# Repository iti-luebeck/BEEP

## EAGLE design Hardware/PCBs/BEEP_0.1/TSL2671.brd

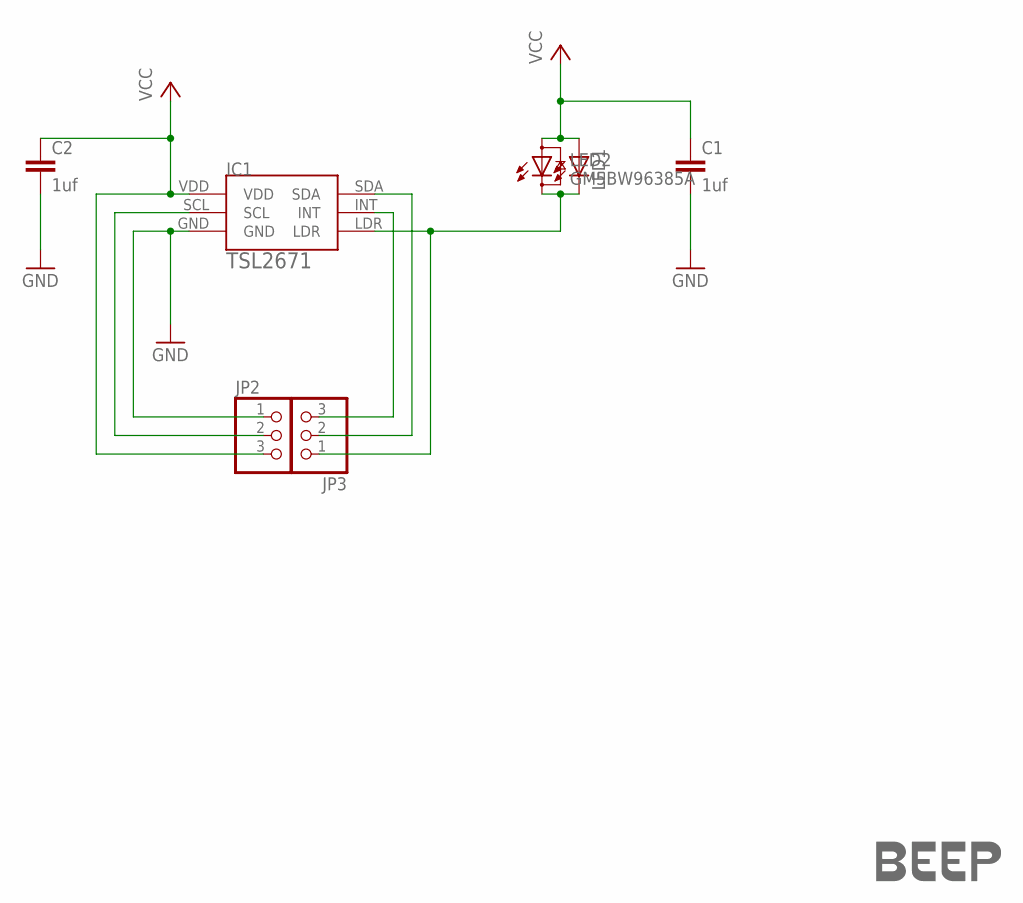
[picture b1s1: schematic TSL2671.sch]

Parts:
C1: 1uf; C025-025X050
C2: 1uf; C1206K
IC1: TSL2671
JP2, JP3: PINHD-1X3; 1X03
LED1: LED5MM
LED2: GM5BW96385A
U$1: LOGO-COPPER4; COPPER4

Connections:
GND: C1.2, C2.2, IC1.GND, JP2.1
unnamed: IC1.LDR, JP3.1, LED1.K (C), LED2.C
unnamed: IC1.SCL, JP2.2
unnamed: IC1.SDA, JP3.2
unnamed: IC1.INT, JP3.3
VCC: C1.1, C2.1, IC1.VDD, JP2.3, LED1.A, LED2.A

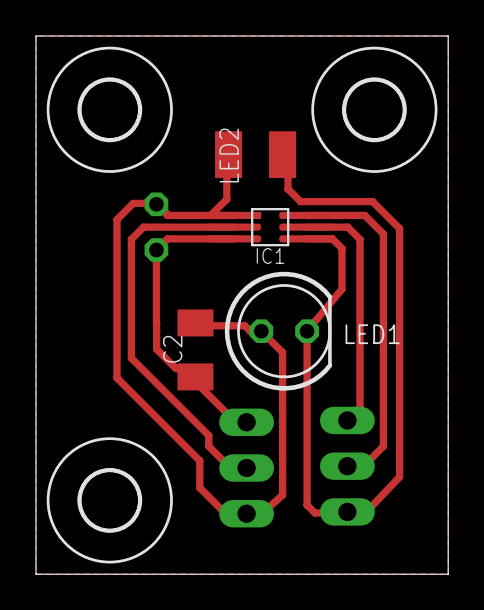
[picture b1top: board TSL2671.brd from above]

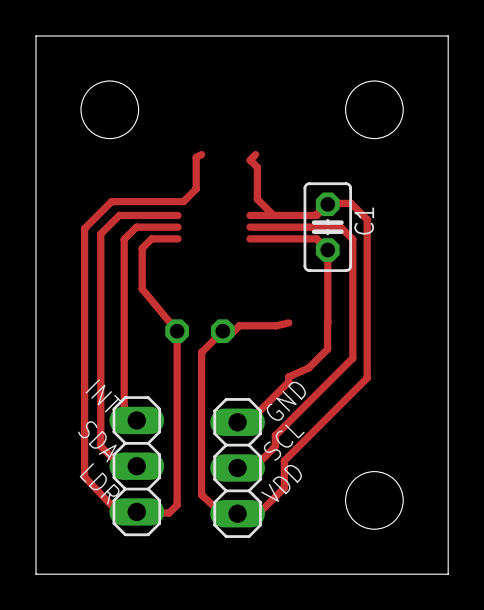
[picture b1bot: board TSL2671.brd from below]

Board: 2 copper layers, 22.9 x 29.9 mm, 11 parts (3 on the bottom side), 6 nets.

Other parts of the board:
U$2, U$3, U$4: 3,2

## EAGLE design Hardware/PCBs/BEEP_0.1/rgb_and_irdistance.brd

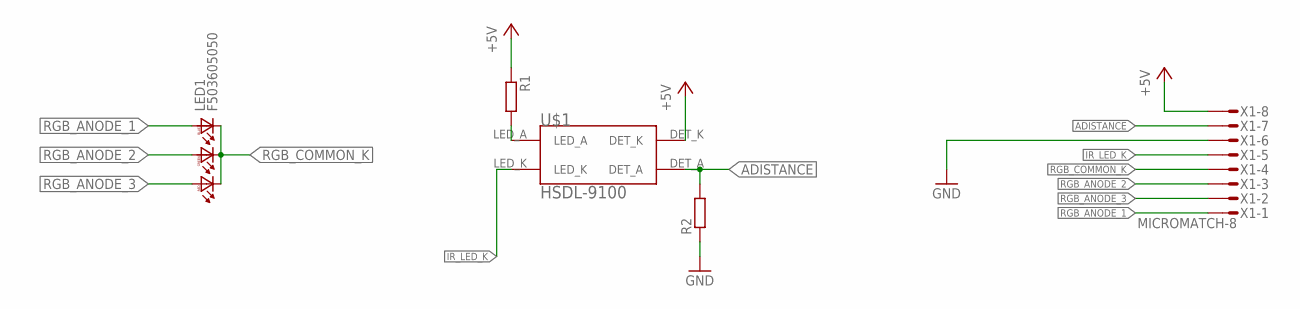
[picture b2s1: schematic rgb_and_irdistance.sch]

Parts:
LED1: F503605050; 5050LED
R1, R2: R-EU_R0603; R0603
U$1: HSDL-9100
X1: MICROMATCH-8

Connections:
+5V: R1.1, U$1.DET_K, X1.8
ADISTANCE: R2.2, U$1.DET_A, X1.7
GND: R2.1, X1.6
IR_LED_K: U$1.LED_K, X1.5
unnamed: R1.2, U$1.LED_A
RGB_ANODE_1: LED1.B1 (BA), X1.1
RGB_ANODE_2: LED1.G1 (GA), X1.3
RGB_ANODE_3: LED1.R1 (RA), X1.2
RGB_COMMON_K: LED1.B2 (BC), LED1.G2 (GC), LED1.R2 (RC), X1.4

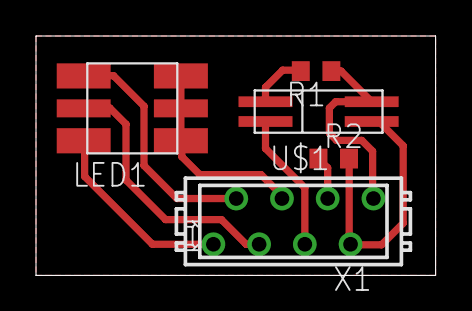
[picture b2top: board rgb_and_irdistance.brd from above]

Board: 2 copper layers, 22.2 x 13.3 mm, 5 parts (0 on the bottom side), 9 nets.

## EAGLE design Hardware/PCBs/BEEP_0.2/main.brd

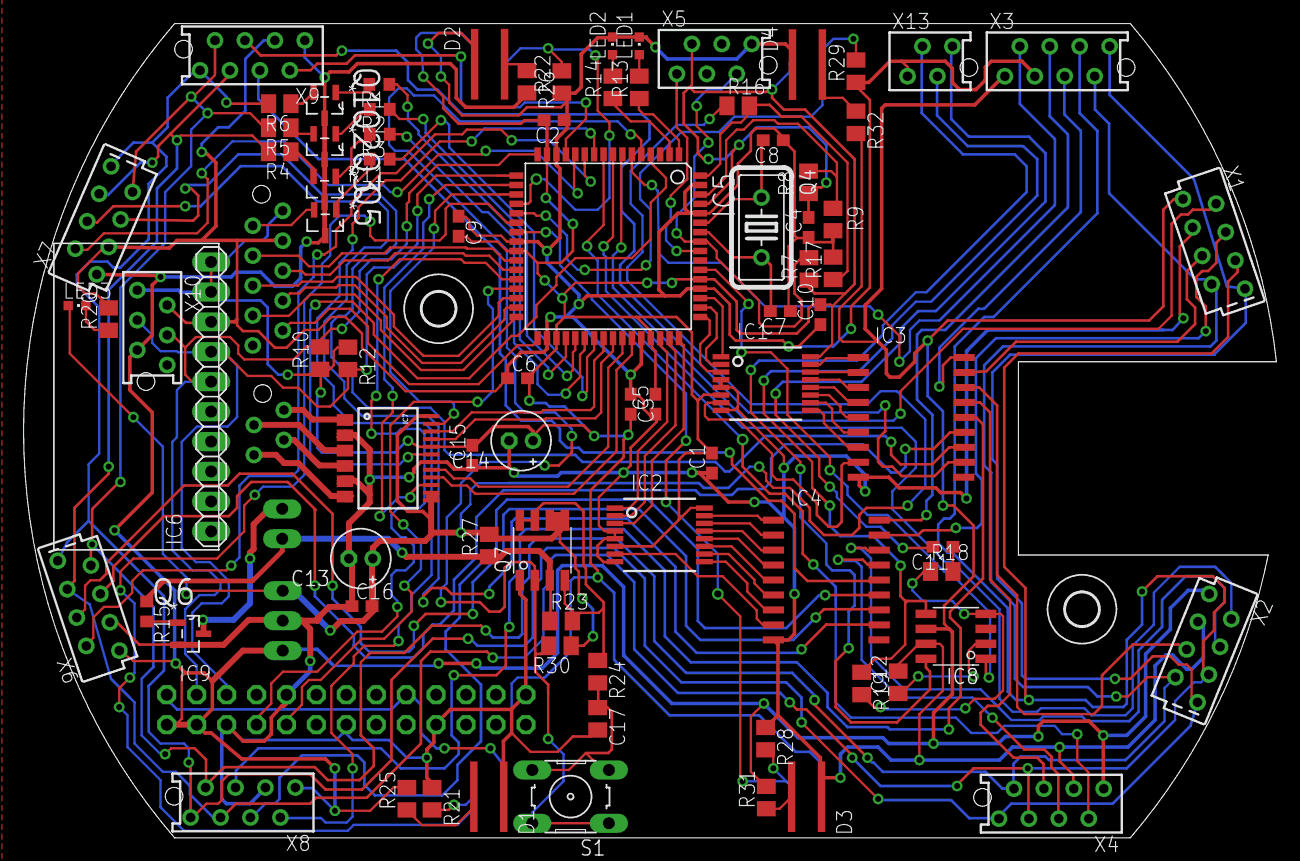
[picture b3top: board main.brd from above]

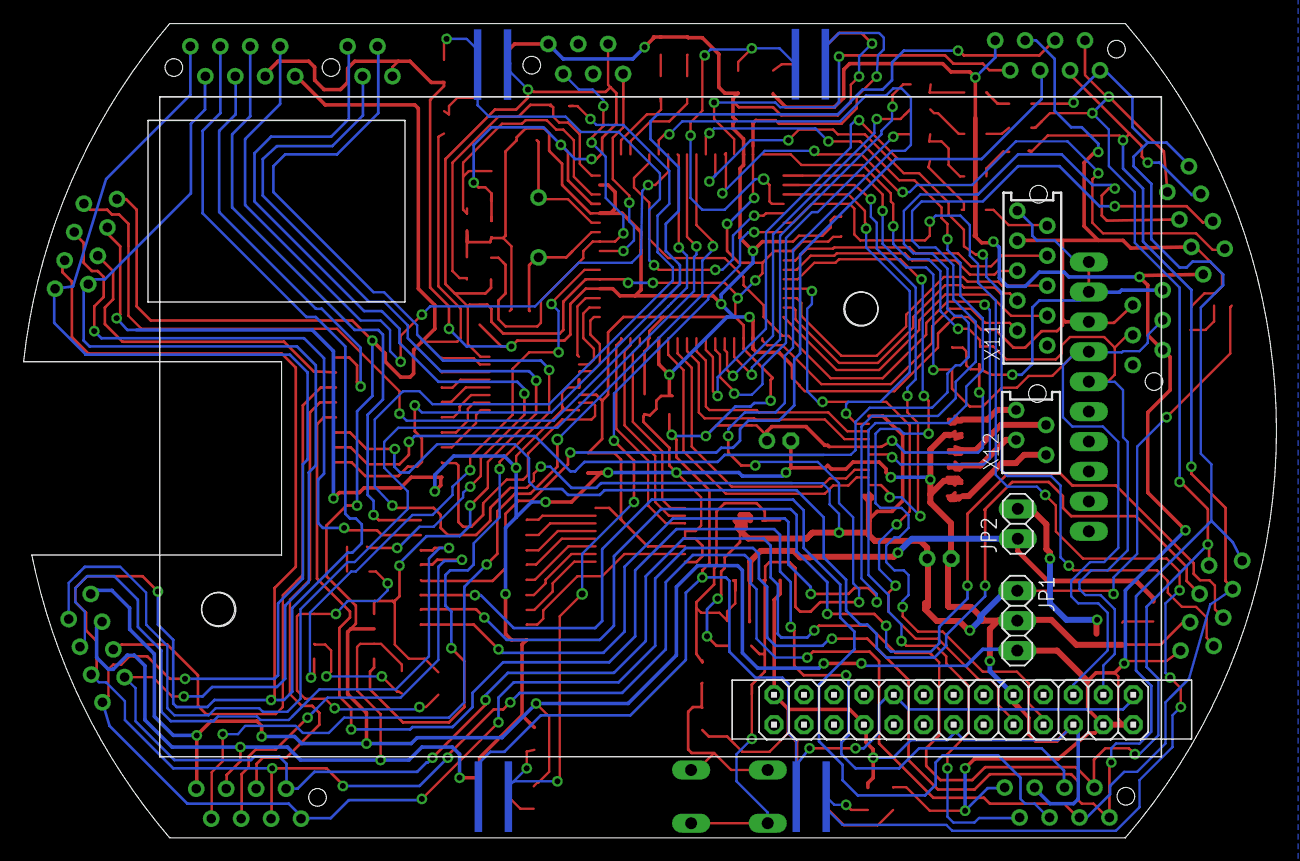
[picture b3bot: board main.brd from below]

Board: 2 copper layers, 106.3 x 69.1 mm, 91 parts (5 on the bottom side), 118 nets.

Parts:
C1, C2, C3, C4, C5, C6, C9, C10, C11, C15, C16: 100nF; C0603
C7, C8: 22pF; C0603
C12: 1uF; M0805
C13, C14: 10uF; E2-5
C17: 4,7uF; M0805
D1, D2, D3, D4: CNY70
IC1, IC2: 74HC238SSOP; SSOP16
IC3, IC4: ULN2803ASOP18; SOP18
IC5: ATXMEGA64D3-AU; TQFP-64A-64
IC6: GY-81
IC7: TB6612FNG; SSOP24
IC8: TS34119SMD; SO08
IC9: RASPBERRY-PI; RASPERRRY-PI
JP1: Step_Down_Conn; 1X03
JP2: batt_conn; 1X02
LED1: YELLOW; CHIPLED_0603
LED2: RED; CHIPLED_0603
LED3: blue; CHIPLED_0603
Q1, Q2, Q3, Q5, Q6: DMN2075U; SOT95P240X112-3N
Q4: 32Mhz; HC18U-V
Q7: DMC3028LSD; SO08
R1, R2, R3, R11, R15: 100R; R0603
R4, R5, R6, R8, R9, R16, R17, R21, R22, R25, R26, R28, R29, R31, R32: M0805
R7: 10K; M0805
R10, R12, R23, R30: 10k; M0805
R13: 220R; M0805
R14: 390R; M0805
R18: 3k; M0805
R19: 75k; M0805
R20: 1K; M0805
R24: 100k; M0805
R27: 0R; M0805
S1: On / Off; B3F-10XX
U$1: COPPER7
U$4, U$6: 2,8
X1: Sens1; FSIDE-8
X2: Sens2; FSIDE-8
X3: Sens0; FTOP-8
X4: Sens3; FTOP-8
X5: PDI interface (ISP); FTOP-6
X6: Sens5; FSIDE-8
X7: Sens6; FSIDE-8
X8: Sens4; FTOP-8
X9: Sens7; FTOP-8
X10: exp header; FTOP-6
X11: line follow; FTOP-10
X12: motor; FTOP-4
X13: audio; FTOP-4

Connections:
+3V3: C1.2, C2.2, C3.2, C4.2, C5.2, C6.2, C9.2, C10.2, C14.+, C15.2, D1.TRANS_C, D2.TRANS_C, D3.TRANS_C, D4.TRANS_C, IC1.6, IC1.16, IC2.6, IC2.16, IC5.15, IC5.25, IC5.35, IC5.45, IC5.53, IC5.61, IC6.3V3, IC6.VCC_IN, IC7.20, IC9.3V3@1, IC9.3V3@2, R7.1, R8.1, R10.1, R12.1, X5.2, X10.1, X11.10
+5V: IC8.6, IC9.5V@1, IC9.5V@2, JP1.3, Q1.D, Q2.D, Q3.D, Q5.D, R25.2, R26.2, R31.2, R32.2, X1.1, X2.1, X3.1, X4.1, X6.1, X7.1, X8.1, X9.1, X10.5
+7V: C13.+, C16.2, IC7.13, IC7.14, IC7.24, JP1.1, LED3.A, Q7.5, Q7.6, R16.1, R27.2, R30.1
ADISTANCE_0: IC5.6, X3.2
ADISTANCE_1: IC5.7, X1.2
ADISTANCE_2: IC5.8, X2.2
ADISTANCE_3: IC5.9, X4.2
ADISTANCE_4: IC5.10, X8.2
ADISTANCE_5: IC5.11, X6.2
ADISTANCE_6: IC5.12, X7.2
ADISTANCE_7: IC5.13, X9.2
AUDIO_DISABLE: IC5.54, IC8.1
AUDIO_IN: C11.2, X13.4
BATT_GND: JP2.2, Q6.D
BATT_U: JP2.1, Q7.3, R15.1, R23.1, R27.1
BATT_VOLTAGE: IC5.64, R16.2, R17.1
BATT_WARN_0: IC5.1, R13.1
BATT_WARN_1: IC5.2, R14.1
COLOR_DIODE_1: IC5.31, X11.4
COLOR_DIODE_2: IC5.32, X11.3
COLOR_FREQ_OUT: IC5.26, X11.7
COLOR_SENSOR_1: IC5.33, X11.2
COLOR_SENSOR_2: IC5.27, X11.6
COLOR_SENSOR_3: IC5.30, X11.5
COLOR_SENSOR_PWM_LED: IC5.39, R11.1
ENCODER_L1: D2.TRANS_E, IC5.20, R22.2
ENCODER_L2: D4.TRANS_E, IC5.21, R29.2
ENCODER_R1: D1.TRANS_E, IC5.22, R21.2
ENCODER_R2: D3.TRANS_E, IC5.23, R28.2
GND: C1.1, C2.1, C3.1, C4.1, C5.1, C6.1, C7.1, C8.1, C9.1, C10.1, C12.2, C13.-, C14.-, C15.1, C16.1, C17.2, D1.LED_C, D2.LED_C, D3.LED_C, D4.LED_C, IC1.4, IC1.5, IC1.8, IC2.4, IC2.5, IC2.8, IC3.9, IC4.9, IC5.14, IC5.24, IC5.34, IC5.44, IC5.52, IC5.60, IC5.63, IC6.GND, IC7.3, IC7.4, IC7.9, IC7.10, IC7.18, IC8.7, IC9.GND@1, IC9.GND@2, IC9.GND@3, IC9.GND@4, IC9.GND@5, JP1.2, LED1.C, LED2.C, Q6.S, Q7.1, R9.2, R17.2, R20.2, R21.1, R22.1, R28.1, R29.1, X1.3, X2.3, X3.3, X4.3, X5.6, X6.3, X7.3, X8.3, X9.3, X10.2, X11.8, X13.1
IR_LED_K0: IC2.15, IC4.1
IR_LED_K0_OUT: IC4.18, X3.4
IR_LED_K1: IC2.14, IC4.2
IR_LED_K1_OUT: IC4.17, X1.4
IR_LED_K2_OUT: IC4.16, X2.4
IR_LED_K3_OUT: IC4.15, X4.4
IR_LED_K4_OUT: IC4.13, X8.4
IR_LED_K5_OUT: IC4.12, X6.4
IR_LED_K6_OUT: IC4.11, X7.4
IR_LED_K7_OUT: IC4.14, X9.4
IR_LED_MK0: IC2.1, IC5.46
IR_LED_MK1: IC2.2, IC5.47
IR_LED_MK2: IC2.3, IC5.48
LED_A0: IC5.36, R1.1
LED_A0_OUT: R6.2, X1.8, X2.8, X3.8, X4.8, X6.8, X7.8, X8.8, X9.8
LED_A1: IC5.37, R2.1
LED_A1_OUT: R5.2, X1.7, X2.7, X3.7, X4.7, X6.7, X7.7, X8.7, X9.7
LED_A2: IC5.38, R3.1
LED_A2_OUT: R4.2, X1.6, X2.6, X3.6, X4.6, X6.6, X7.6, X8.6, X9.6
LED_K0_OUT: IC3.18, X3.5
LED_K1_OUT: IC3.17, X1.5
LED_K2_OUT: IC3.16, X2.5
LED_K3_OUT: IC3.15, X4.5
LED_K4_OUT: IC3.14, X8.5
LED_K5_OUT: IC3.13, X6.5
LED_K6_OUT: IC3.12, X7.5
LED_K7_OUT: IC3.11, X9.5
MOTOR_A_IN1: IC5.41, IC7.21
MOTOR_A_IN2: IC5.40, IC7.22
MOTOR_A_OUT1: IC7.1, IC7.2, X12.4
MOTOR_A_OUT2: IC7.5, IC7.6, X12.3
MOTOR_A_PWM: IC5.19, IC7.23
MOTOR_B_IN1: IC5.42, IC7.17
MOTOR_B_IN2: IC5.43, IC7.16
MOTOR_B_OUT1: IC7.11, IC7.12, X12.1
MOTOR_B_OUT2: IC7.7, IC7.8, X12.2
MOTOR_B_PWM: IC5.18, IC7.15
MOTOR_STBY: IC5.4, IC7.19
unnamed: Q3.S, R4.1
unnamed: Q2.S, R5.1
unnamed: Q1.S, R6.1
unnamed: IC5.62, R8.2, R9.1
unnamed: Q5.S, X11.9
unnamed: IC2.13, IC4.3
unnamed: IC2.12, IC4.4
unnamed: Q6.G, R15.2
unnamed: IC2.11, IC4.5
unnamed: IC2.10, IC4.6
unnamed: D4.LED_A, R32.1
unnamed: IC2.9, IC4.7
unnamed: IC2.7, IC4.8
unnamed: C8.2, IC5.59, Q4.1
unnamed: IC8.4, R18.1, R19.2
unnamed: C17.1, R24.2, S1.3, S1.4
unnamed: C11.1, R18.2
unnamed: C7.2, IC5.58, Q4.2
unnamed: LED3.C, R20.1
unnamed: D1.LED_A, R25.1
unnamed: IC1.15, IC3.1
unnamed: Q7.4, Q7.7, Q7.8, R23.2, R24.1
unnamed: D2.LED_A, R26.1
unnamed: IC1.14, IC3.2
unnamed: Q5.G, R11.2
unnamed: D3.LED_A, R31.1
unnamed: IC1.13, IC3.3
unnamed: IC1.12, IC3.4
unnamed: LED2.A, R14.2
unnamed: IC1.11, IC3.5
unnamed: IC1.10, IC3.6
unnamed: LED1.A, R13.2
unnamed: IC1.9, IC3.7
unnamed: IC1.7, IC3.8
unnamed: C12.1, IC8.2
unnamed: Q1.G, R1.2
unnamed: Q2.G, R2.2
unnamed: Q3.G, R3.2
PDI_CLK: IC5.57, R7.2, X5.5
PDI_DATA: IC5.56, X5.1
POWER_OFF: IC5.5, Q7.2, R30.2, S1.1, S1.2
RGB_LED_MK0: IC1.1, IC5.51
RGB_LED_MK1: IC1.2, IC5.50
RGB_LED_MK2: IC1.3, IC5.49
RPI_RX: IC5.29, IC9.GPIO_15
RPI_TX: IC5.28, IC9.GPIO_14
SCL: IC5.17, IC6.SCL, IC9.GPIO_1, R12.2, X10.3
SDA: IC5.16, IC6.SDA, IC9.GPIO_0, R10.2, X10.4
SPEAKER_O1: IC8.8, X13.2
SPEAKER_O2: IC8.5, R19.1, X13.3

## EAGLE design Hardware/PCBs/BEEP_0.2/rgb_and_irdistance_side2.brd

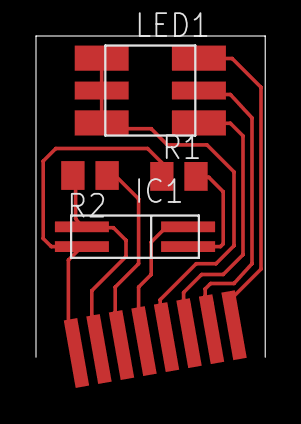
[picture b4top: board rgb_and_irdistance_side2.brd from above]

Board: 2 copper layers, 12.7 x 17.9 mm, 5 parts (0 on the bottom side), 9 nets.

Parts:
IC1: HSDL-9100
LED1: F503605050; 5050LED
R1, R2: M0805
U$1: 8PIN_CABLE_SOLDER

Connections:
+5V: IC1.DET_K, R1.1, U$1.P$1
ADISTANCE: IC1.DET_A, R2.2, U$1.P$2
GND: R2.1, U$1.P$3
IR_LED_K: IC1.LED_K, U$1.P$4
unnamed: IC1.LED_A, R1.2
RGB_ANODE_1: LED1.B1, U$1.P$8
RGB_ANODE_2: LED1.G1, U$1.P$7
RGB_ANODE_3: LED1.R1, U$1.P$6
RGB_COMMON_K: LED1.B2, LED1.G2, LED1.R2, U$1.P$5

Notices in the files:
parts and their libraries:
SparkFun-PowerIC: Licensing: CC v3.0 Share-Alike You are welcome to use this library for commercial purposes.
